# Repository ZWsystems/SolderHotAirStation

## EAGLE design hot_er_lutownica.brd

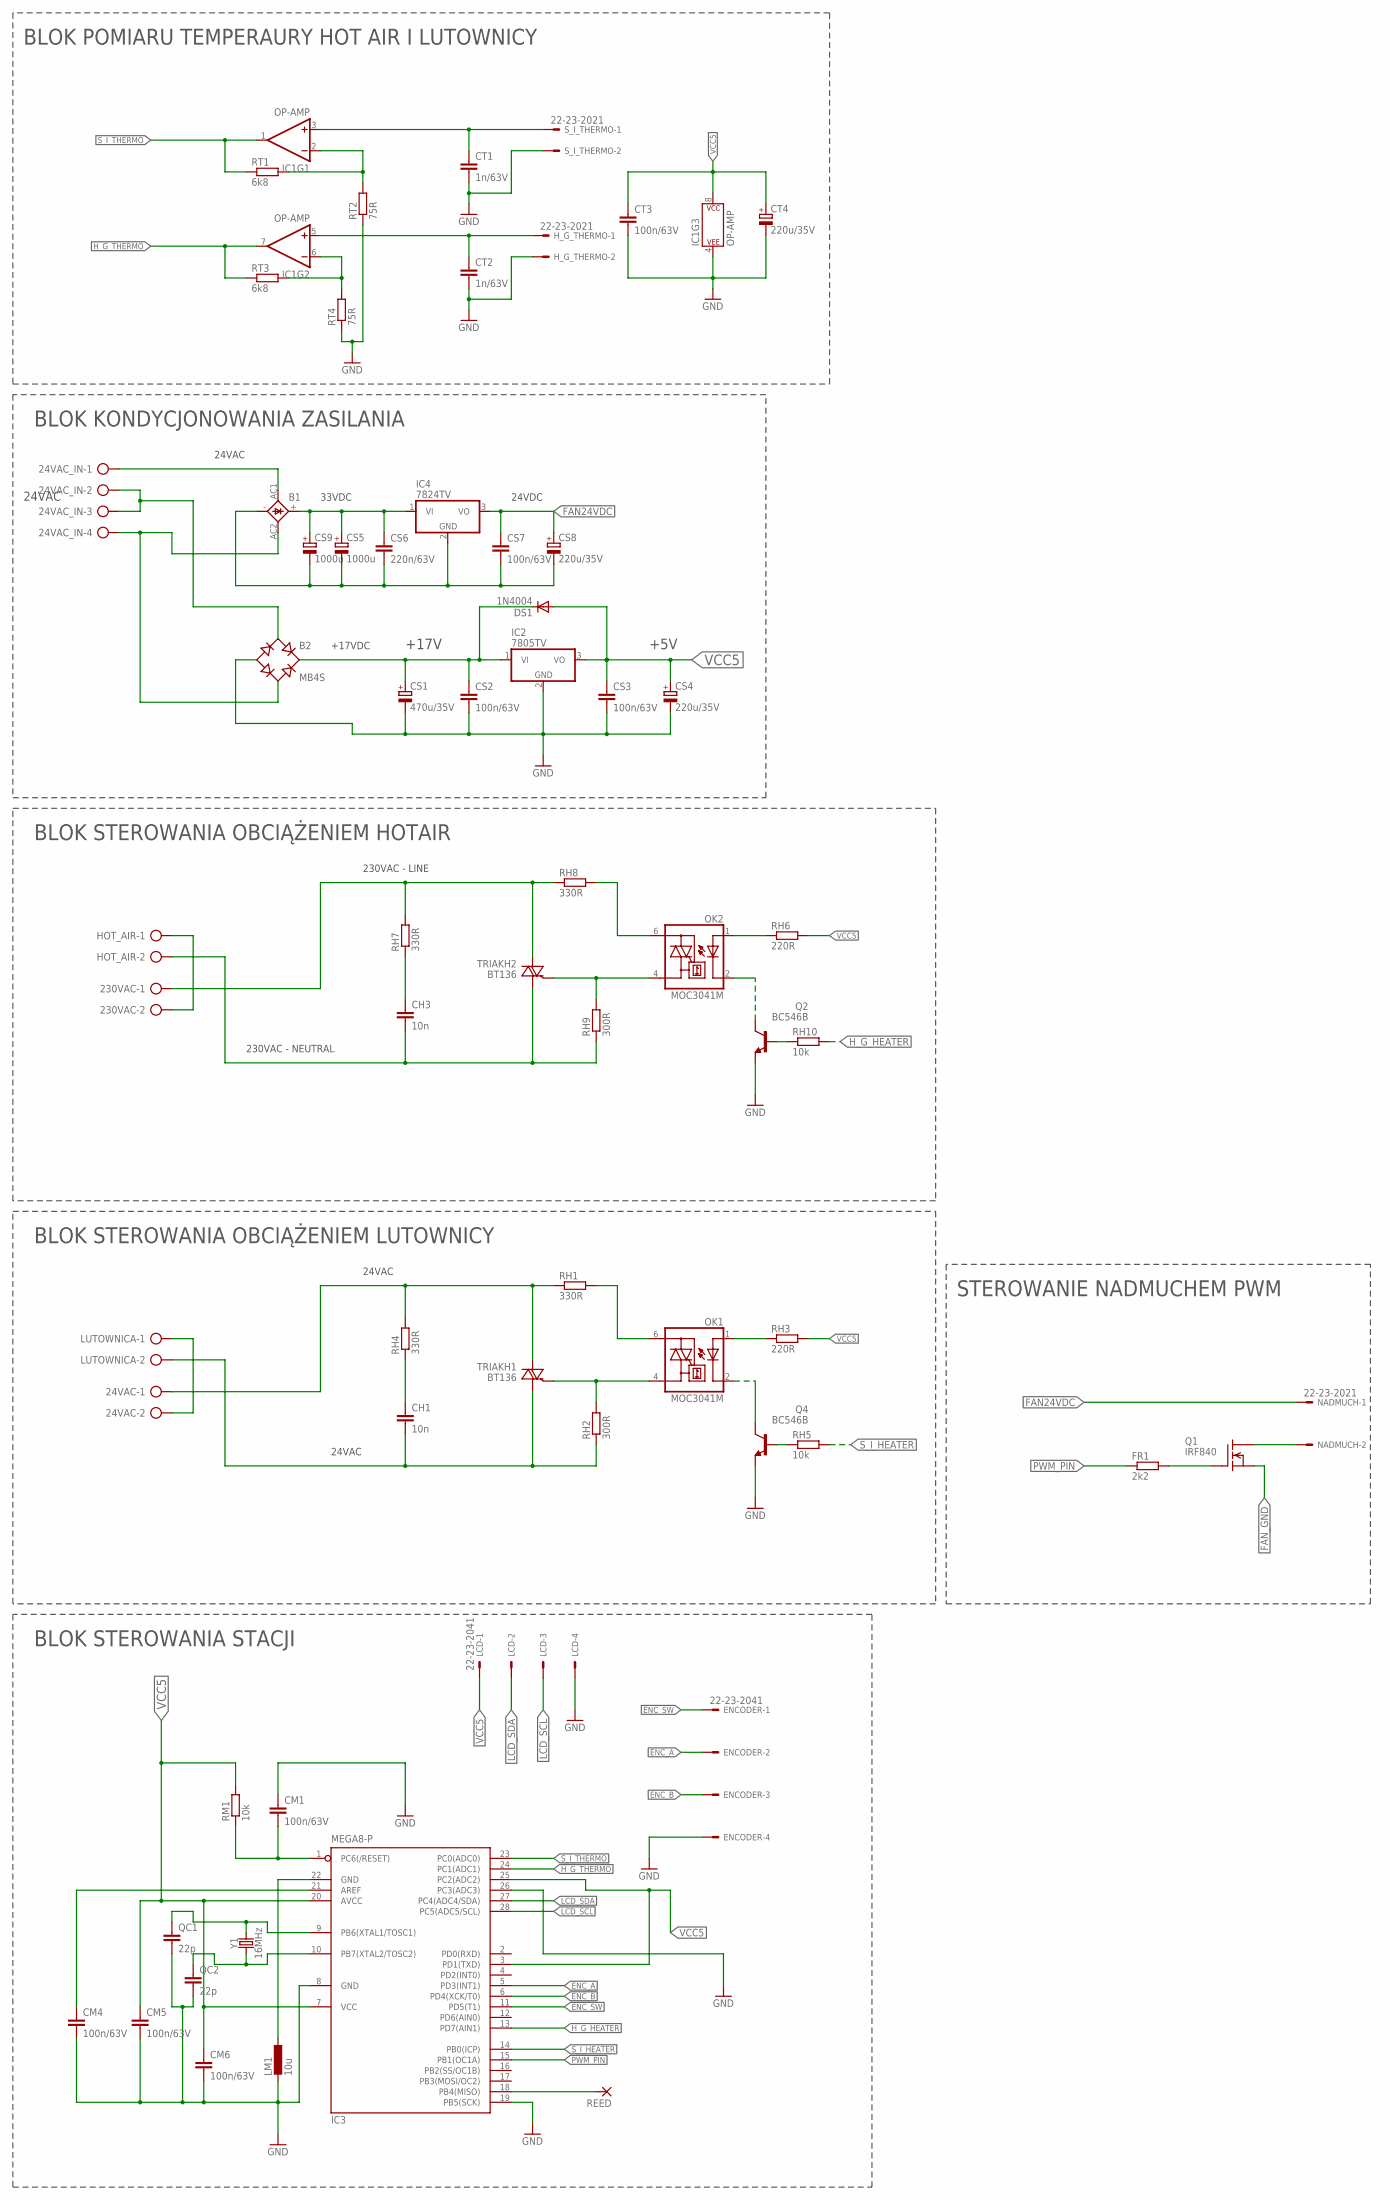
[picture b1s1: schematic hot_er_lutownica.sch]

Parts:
24VAC, 230VAC: AK500/2
24VAC_IN: AK500/4
B1: 2KBB-R
B2: MB4S; SOIC-4
CH1, CH3: 10n; C102-043X133
CM1, CM4, CM5, CM6: 100n/63V; C050-024X044
CS1: 470u/35V; B45181A
CS2, CS3, CS7: 100n/63V; C050-024X044
CS4, CS8: 220u/35V; B45181A
CS5, CS9: 1000u; E3,5-8
CS6: 220n/63V; C050-024X044
CT1, CT2: 1n/63V; C050-024X044
CT3: 100n/63V; C050-024X044
CT4: 220u/35V; B45181B
DS1: 1N4004; DO41-10
ENCODER: 22-23-2041
FR1: 2k2; R0805
HOT_AIR: AK500/2
H_G_THERMO: 22-23-2021
IC1: OP-AMP; DIP08
IC2: 7805TV; TO220V
IC3: MEGA8-P; DIL28-3
IC4: 7824TV; TO220V
LCD: 22-23-2041
LM1: 10u; 0207/10
LUTOWNICA: AK500/2
NADMUCH: 22-23-2021
OK1, OK2: MOC3041M; DIL06
Q1: IRF840; TO220
Q2, Q4: BC546B; TO92-EBC
QC1, QC2: 22p; C0805K
REED: 2,54/0,9
RH1, RH7: 330R; 0204/7
RH2, RH9: 300R; 0204/5
RH3: 220R; 0204/5
RH4: 330R; 0204/5
RH5: 10k; 0204/7
RH6: 220R; 0204/7
RH8: 330R; 0207/10
RH10: 10k; 0207/12
RM1: 10k; R0805
RT1, RT3: 6k8; 0207/2V
RT2, RT4: 75R; 0207/2V
S_I_THERMO: 22-23-2021
TRIAKH1, TRIAKH2: BT136; TO220AB
Y1: 16MHz; HC49U

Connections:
230NEUTRAL: 230VAC.2, HOT_AIR.1
AGND: IC3.22 (GND), LM1.1
COSZEBYBYLODLUGIE: CH3.1, RH7.1
ENC_A: ENCODER.2, IC3.5 (PD3(INT1))
ENC_B: ENCODER.3, IC3.6 (PD4(XCK/T0))
ENC_SW: ENCODER.1, IC3.11 (PD5(T1))
FAN24VDC: CS7.1, CS8.+, IC4.3 (VO), NADMUCH.1
FAN_GND: B1.-, CS5.-, CS6.2, CS7.2, CS8.-, CS9.-, IC4.2 (GND), Q1.3 (S)
GATEHOT: OK2.4 (A1), RH9.2, TRIAKH2.3 (G)
GATELUT: OK1.4 (A1), RH2.2, TRIAKH1.3 (G)
GND: B2.-, CM1.1, CM4.2, CM5.2, CM6.2, CS1.-, CS2.2, CS3.2, CS4.-, CT1.2, CT2.2, CT3.2, CT4.-, ENCODER.4, H_G_THERMO.2, IC1.4 (P$V-), IC2.2 (GND), IC3.8 (GND), IC3.19 (PB5(SCK)), IC3.26 (PC3(ADC3)), LCD.4, LM1.2, Q2.E, Q4.E, QC1.2, QC2.2, RT2.1, RT4.1, S_I_THERMO.2
HEATER_L: CH1.2, LUTOWNICA.2, RH2.1, TRIAKH1.1 (A1)
HEATER_L1: CH3.2, HOT_AIR.2, RH9.1, TRIAKH2.1 (A1)
HG_THERMO: CT2.1, H_G_THERMO.1, IC1.5 (+IN)
H_G_HEATER: IC3.13 (PD7(AIN1)), RH10.2
H_G_THERMO: IC1.7 (OUT), IC3.24 (PC1(ADC1)), RT3.1
LCD_SCL: IC3.28 (PC5(ADC5/SCL)), LCD.3
LCD_SDA: IC3.27 (PC4(ADC4/SDA)), LCD.2
MAIN_L: 24VAC.1, RH1.1, RH4.2, TRIAKH1.2 (A2)
MAIN_L1: 230VAC.1, RH7.2, RH8.1, TRIAKH2.2 (A2)
MAIN_N: 24VAC.2, LUTOWNICA.1
unnamed: IC3.9 (PB6(XTAL1/TOSC1)), QC1.1, Y1.2
unnamed: IC3.10 (PB7(XTAL2/TOSC2)), QC2.1, Y1.1
unnamed: OK1.1 (A), RH3.1
unnamed: OK2.6 (A2), RH8.2
unnamed: OK2.1 (A), RH6.1
unnamed: IC1.6 (-IN), RT3.2, RT4.2
unnamed: NADMUCH.2, Q1.2 (D)
unnamed: IC1.2 (-IN), RT1.2, RT2.2
unnamed: 24VAC_IN.1, B1.AC1
unnamed: FR1.2, Q1.1 (G)
unnamed: OK2.2 (C), Q2.C
unnamed: OK1.6 (A2), RH1.2
unnamed: Q2.B, RH10.1
unnamed: 24VAC_IN.2, 24VAC_IN.3, B2.~1 (AC1)
unnamed: 24VAC_IN.4, B1.AC2, B2.~2 (AC2)
unnamed: OK1.2 (C), Q4.C
unnamed: Q4.B, RH5.1
unnamed: CH1.1, RH4.1
POS17V: B2.+, CS1.+, CS2.1, DS1.C, IC2.1 (VI)
POS33V: B1.+, CS5.+, CS6.1, CS9.+, IC4.1 (VI)
PWM_PIN: FR1.1, IC3.15 (PB1(OC1A))
REED: IC3.18 (PB4(MISO)), REED.1
REFERENCE: CM4.1, IC3.21 (AREF)
RESET: CM1.2, IC3.1 (PC6(/RESET)), RM1.1
SI_THERMO: CT1.1, IC1.3 (+IN), S_I_THERMO.1
S_I_HEATER: IC3.14 (PB0(ICP)), RH5.2
S_I_THERMO: IC1.1 (OUT), IC3.23 (PC0(ADC0)), RT1.1
VCC5: CM5.1, CM6.1, CS3.1, CS4.+, CT3.1, CT4.+, DS1.A, IC1.8 (P$V+), IC2.3 (VO), IC3.3 (PD1(TXD)), IC3.7 (VCC), IC3.20 (AVCC), IC3.25 (PC2(ADC2)), LCD.1, RH3.2, RH6.2, RM1.2

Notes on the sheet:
+5V
+17V
24VAC
BLOK STEROWANIA OBCIĄŻENIEM LUTOWNICY
230VAC - LINE
BLOK STEROWANIA OBCIĄŻENIEM HOTAIR
BLOK POMIARU TEMPERAURY HOT AIR I LUTOWNICY
BLOK KONDYCJONOWANIA ZASILANIA
33VDC
24VDC
230VAC - NEUTRAL
+17VDC
STEROWANIE NADMUCHEM PWM
BLOK STEROWANIA STACJI

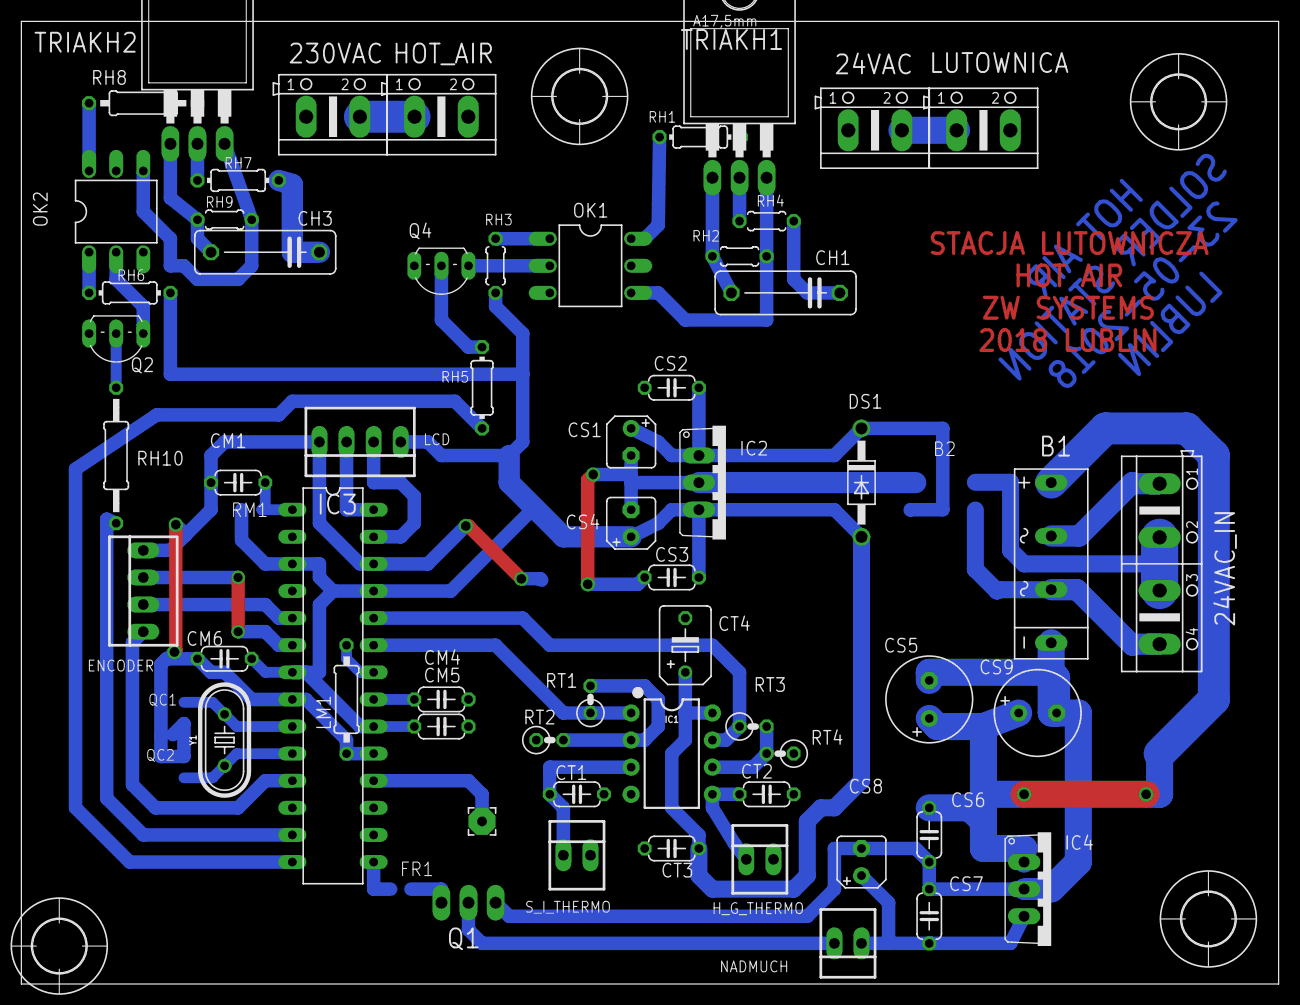
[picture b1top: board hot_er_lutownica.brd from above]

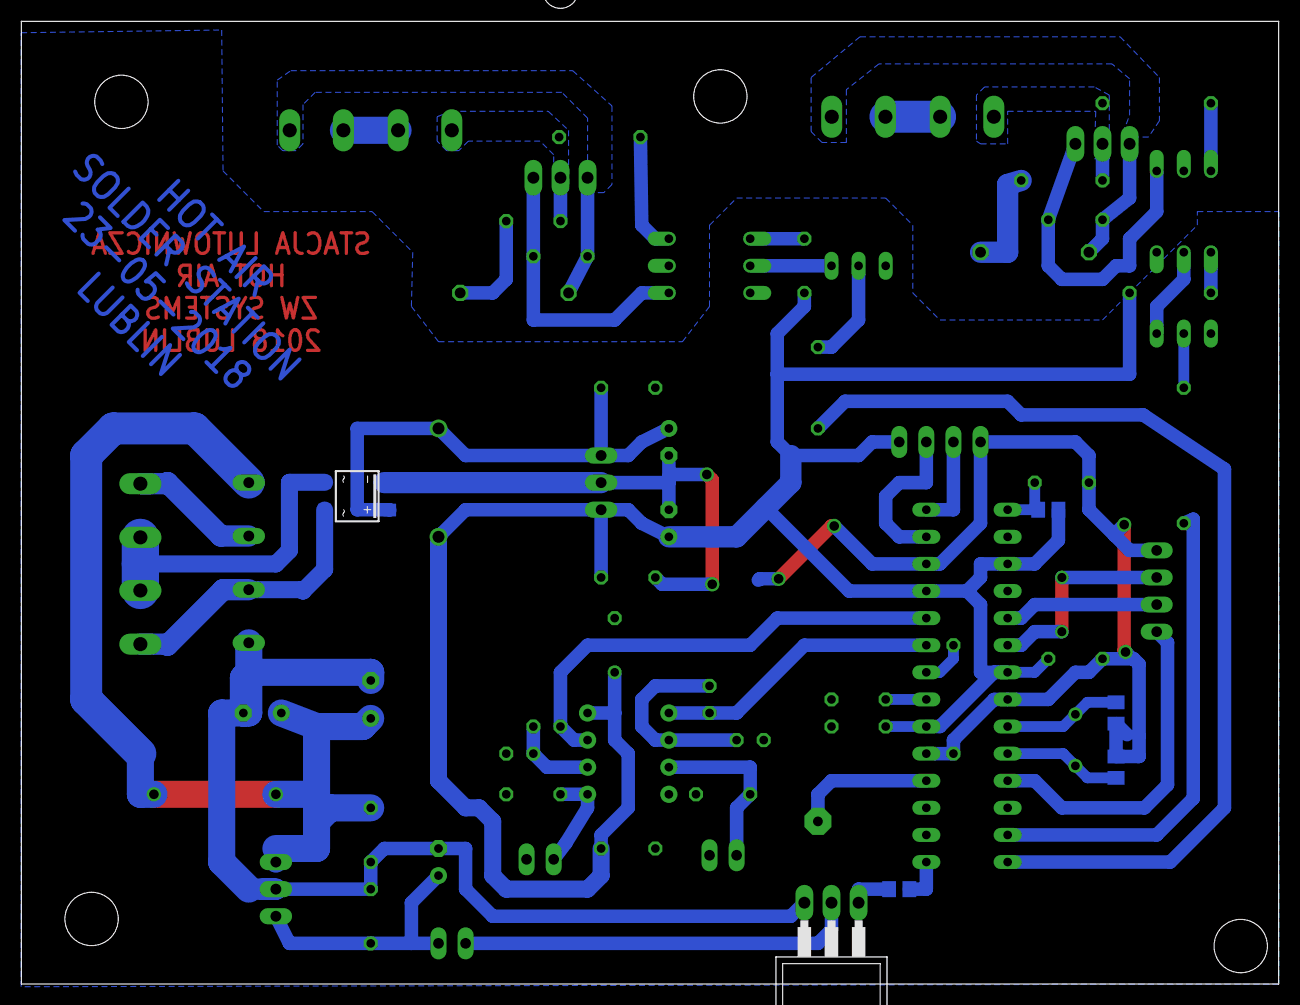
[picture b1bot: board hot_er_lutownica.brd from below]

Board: 2 copper layers, 117.8 x 90.2 mm, 68 parts (6 on the bottom side), 49 nets.

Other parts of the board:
U$1, U$2, U$3, U$4: 5,0

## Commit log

2018-05-26 START

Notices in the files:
parts and their libraries:
SparkFun-IC-Amplifiers: Licensing: Creative Commons ShareAlike 4.0 International - https://creativecommons.org/licenses/by-sa/4.0
